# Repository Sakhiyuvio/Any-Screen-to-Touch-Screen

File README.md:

# Any-Screen-to-Touch-Screen

Making any screen of any device to become touch-screen. Utilizing UWB transceivers for location distinction with triangulation and TWR algorithms. Our pen enclosure communicates to host device via Bluetooth HID.

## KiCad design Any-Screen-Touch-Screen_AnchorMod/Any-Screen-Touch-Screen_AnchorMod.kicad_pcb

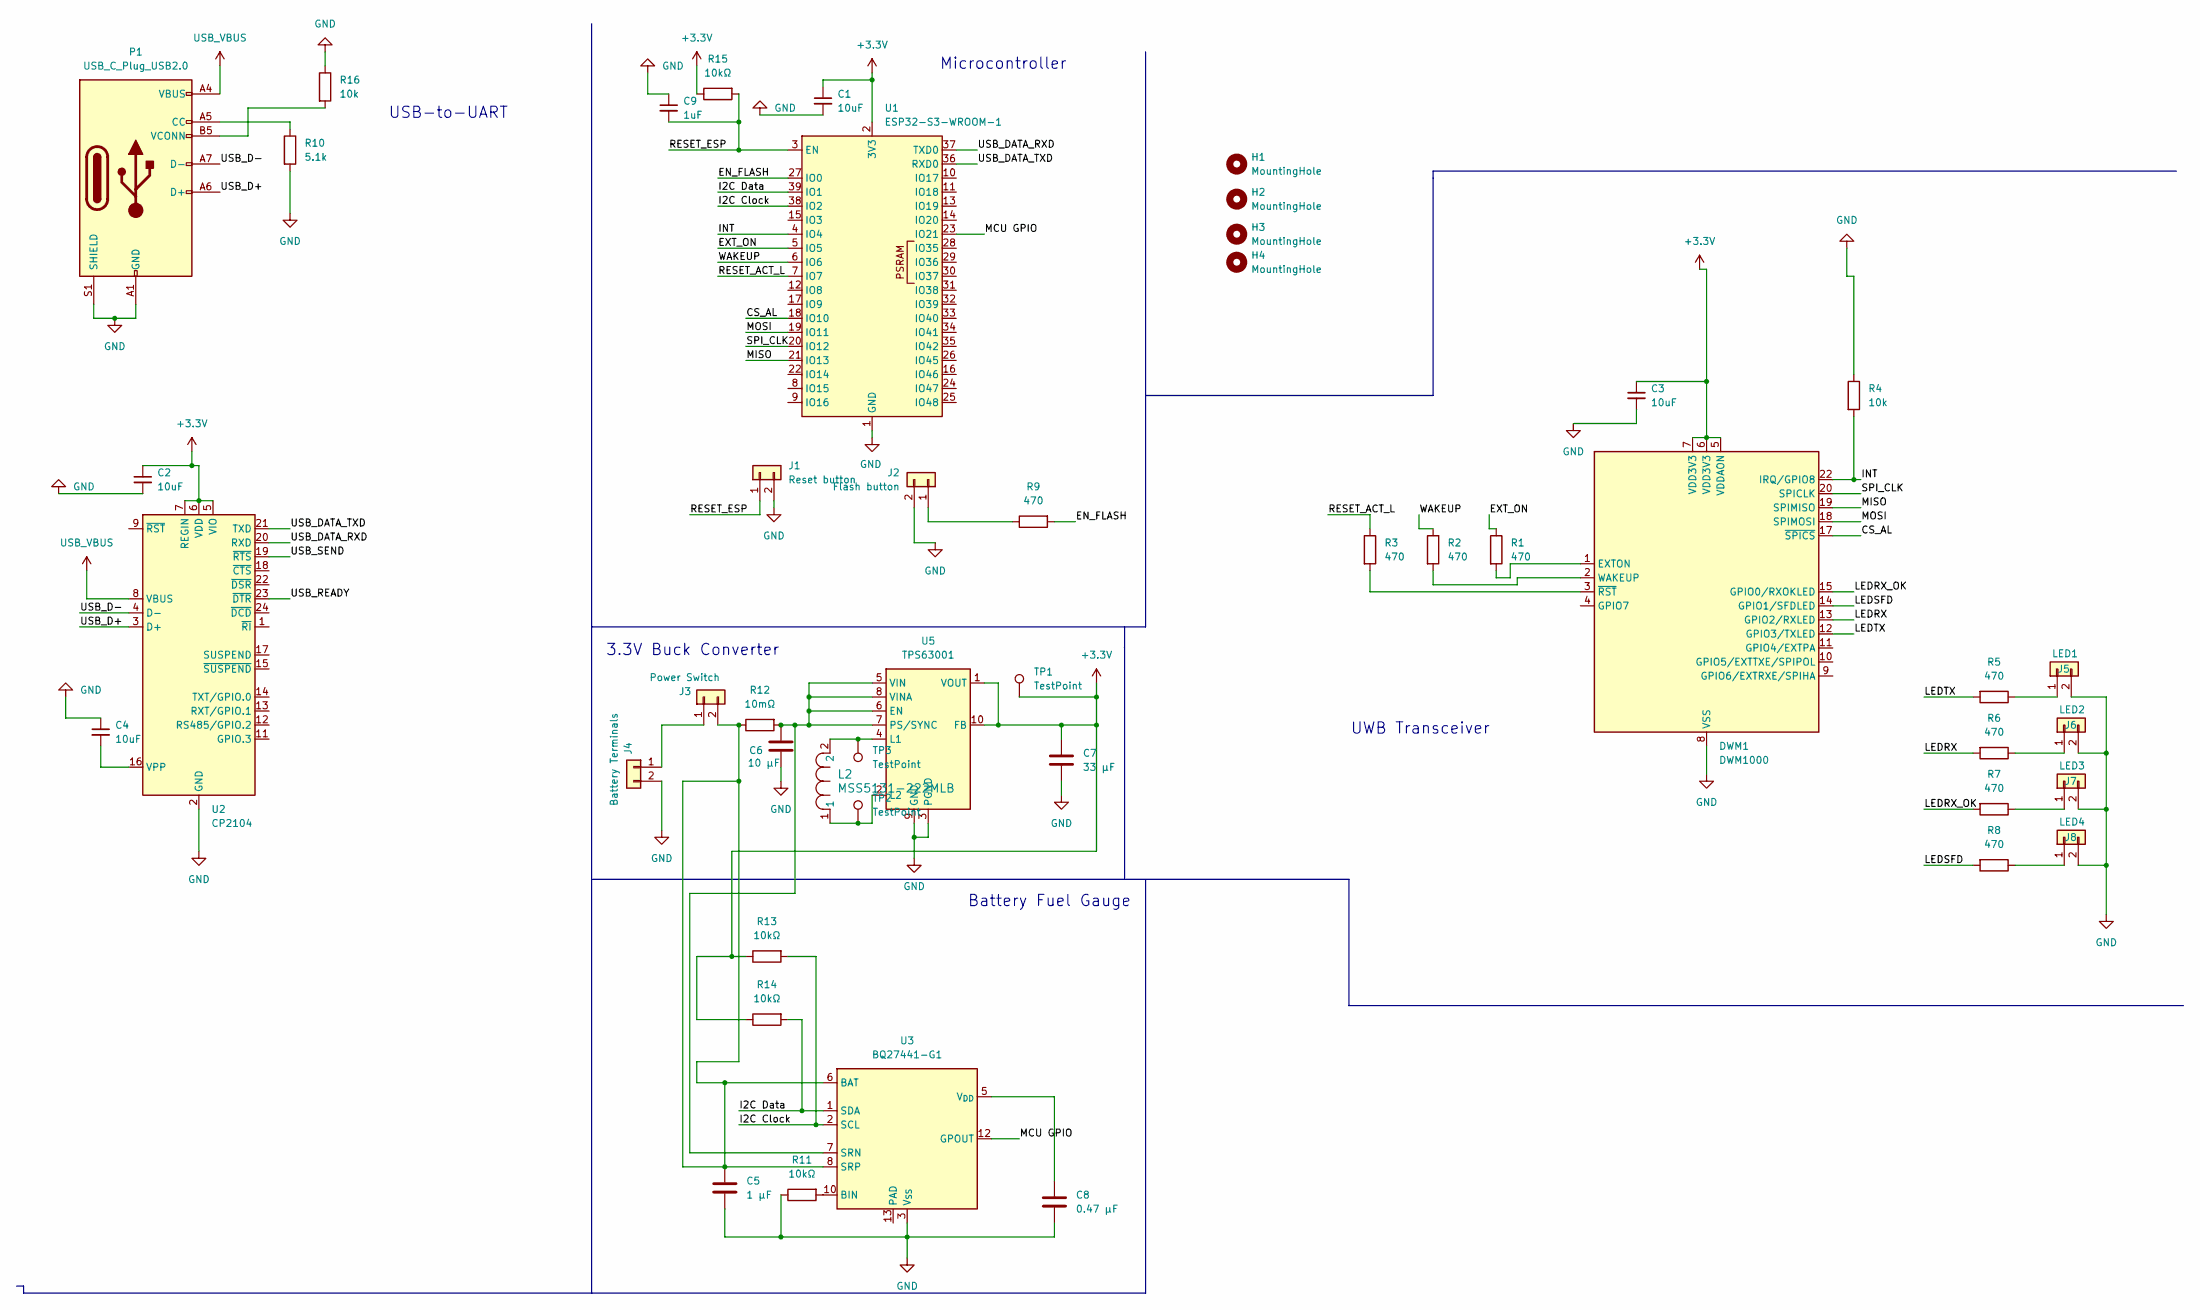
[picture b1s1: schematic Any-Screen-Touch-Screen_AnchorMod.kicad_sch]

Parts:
C1, C2, C3, C4: 10uF; C_0805_2012Metric_Pad1.18x1.45mm_HandSolder
C5: 1 μF; C_0805_2012Metric_Pad1.18x1.45mm_HandSolder
C6: 10 μF; C_0805_2012Metric_Pad1.18x1.45mm_HandSolder
C7: 33 μF; C_0805_2012Metric_Pad1.18x1.45mm_HandSolder
C8: 0.47 μF; C_0805_2012Metric_Pad1.18x1.45mm_HandSolder
C9: 1uF; C_0805_2012Metric_Pad1.18x1.45mm_HandSolder
DWM1: DWM1000
H1, H2, H3, H4: MountingHole; MountingHole_3.2mm_M3
J1: Reset button; Molex_KK-254_AE-6410-02A_1x02_P2.54mm_Vertical
J2: Flash button; Molex_KK-254_AE-6410-02A_1x02_P2.54mm_Vertical
J3: Power Switch; Molex_KK-254_AE-6410-02A_1x02_P2.54mm_Vertical
J4: Battery Terminals; Molex_KK-254_AE-6410-02A_1x02_P2.54mm_Vertical
J5: LED1; Molex_KK-254_AE-6410-02A_1x02_P2.54mm_Vertical
J6: LED2; Molex_KK-254_AE-6410-02A_1x02_P2.54mm_Vertical
J7: LED3; Molex_KK-254_AE-6410-02A_1x02_P2.54mm_Vertical
J8: LED4; Molex_KK-254_AE-6410-02A_1x02_P2.54mm_Vertical
L2: MSS5131-222MLB; IND_MSS5131_COC
P1: USB_C_Plug_USB2.0; USB_C_Plug_Molex_105444
R1, R2, R3, R5, R6, R7, R8, R9: 470; R_0805_2012Metric_Pad1.20x1.40mm_HandSolder
R4, R16: 10k; R_0805_2012Metric_Pad1.20x1.40mm_HandSolder
R10: 5.1k; R_0805_2012Metric_Pad1.20x1.40mm_HandSolder
R11, R13, R14, R15: 10kΩ; R_0805_2012Metric_Pad1.20x1.40mm_HandSolder
R12: 10mΩ; R_0805_2012Metric_Pad1.20x1.40mm_HandSolder
TP1, TP2, TP3: TestPoint; TestPoint_Keystone_5010-5014_Multipurpose
U1: ESP32-S3-WROOM-1
U2: CP2104; QFN-24-1EP_4x4mm_P0.5mm_EP2.7x2.7mm_ThermalVias
U3: BQ27441-G1; Texas_S-PDSO-N12
U5: TPS63001; Texas_DRC0010J_ThermalVias

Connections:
+3.3V: C1.1, C2.1, C3.1, C7.1, DWM1.5 (VDDAON), DWM1.6 (VDD3V3), DWM1.7 (VDD3V3), R13.1, R14.1, R15.1, TP1.1, U1.2 (3V3), U2.5 (VIO), U2.6 (VDD), U2.7 (REGIN), U5.1 (VOUT), U5.10 (FB)
/CS_AL: DWM1.17 (~SPICS), U1.18 (IO10)
/EN_FLASH: R9.2, U1.27 (IO0)
/EXT_ON: R1.1, U1.5 (IO5)
/I2C Clock: R13.2, U1.38 (IO2), U3.2 (SCL)
/I2C Data: R14.2, U1.39 (IO1), U3.1 (SDA)
/INT: DWM1.22 (IRQ/GPIO8), R4.2, U1.4 (IO4)
/LEDRX: DWM1.13 (GPIO2/RXLED), R6.2
/LEDRX_OK: DWM1.15 (GPIO0/RXOKLED), R7.2
/LEDSFD: DWM1.14 (GPIO1/SFDLED), R8.2
/LEDTX: DWM1.12 (GPIO3/TXLED), R5.2
/MCU GPIO: U1.23 (IO21), U3.12 (GPOUT)
/MISO: DWM1.19 (SPIMISO), U1.21 (IO13)
/MOSI: DWM1.18 (SPIMOSI), U1.19 (IO11)
/RESET_ACT_L: R3.1, U1.7 (IO7)
/RESET_ESP: C9.2, J1.1, R15.2, U1.3 (EN)
/SPI_CLK: DWM1.20 (SPICLK), U1.20 (IO12)
/USB_D+: P1.A6 (D+), U2.3 (D+)
/USB_D-: P1.A7 (D-), U2.4 (D-)
/USB_DATA_RXD: U1.37 (TXD0), U2.20 (RXD)
/USB_DATA_TXD: U1.36 (RXD0), U2.21 (TXD)
/USB_READY: U2.23 (~DTR)
/USB_SEND: U2.19 (~RTS)
/WAKEUP: R2.1, U1.6 (IO6)
GND: C1.2, C2.2, C3.2, C4.1, C5.2, C6.1, C7.2, C8.2, C9.1, DWM1.8 (VSS), DWM1.16 (VSS), DWM1.21 (VSS), DWM1.23 (VSS), DWM1.24 (VSS), J1.2, J2.2, J4.2, J5.2, J6.2, J7.2, J8.2, P1.A1 (GND), P1.A12 (GND), P1.B1 (GND), P1.B12 (GND), P1.S1 (SHIELD), R4.1, R10.2, R11.1, R16.1, U1.1 (GND), U1.40 (GND), U1.41 (GND), U2.2 (GND), U2.25 (GND), U3.3 (V_{SS}), U5.3 (PGND), U5.9 (GND), U5.11 (PGND)
unnamed: DWM1.1 (EXTON), R1.2
unnamed: DWM1.2 (WAKEUP), R2.2
unnamed: DWM1.3 (~RST), R3.2
unnamed: J2.1, R9.1
unnamed: J3.1, J4.1
unnamed: C5.1, J3.2, R12.1, U3.6 (BAT), U3.8 (SRP)
unnamed: J5.1, R5.1
unnamed: J6.1, R6.1
unnamed: J7.1, R7.1
unnamed: J8.1, R8.1
unnamed: P1.A5 (CC), R10.1
unnamed: P1.B5 (VCONN), R16.2
unnamed: C4.2, U2.16 (VPP)
unnamed: R11.2, U3.10 (BIN)
unnamed: C6.2, R12.2, U3.7 (SRN), U5.5 (VIN), U5.6 (EN), U5.7 (PS/SYNC), U5.8 (VINA)
unnamed: C8.1, U3.5 (V_{DD})
unnamed: L2.2, TP3.1, U5.4 (L1)
unnamed: L2.1, TP2.1, U5.2 (L2)
USB_VBUS: P1.A4 (VBUS), P1.A9 (VBUS), P1.B4 (VBUS), P1.B9 (VBUS), U2.8 (VBUS)

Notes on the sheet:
USB-to-UART
Microcontroller
3.3V Buck Converter
Battery Fuel Gauge
UWB Transceiver

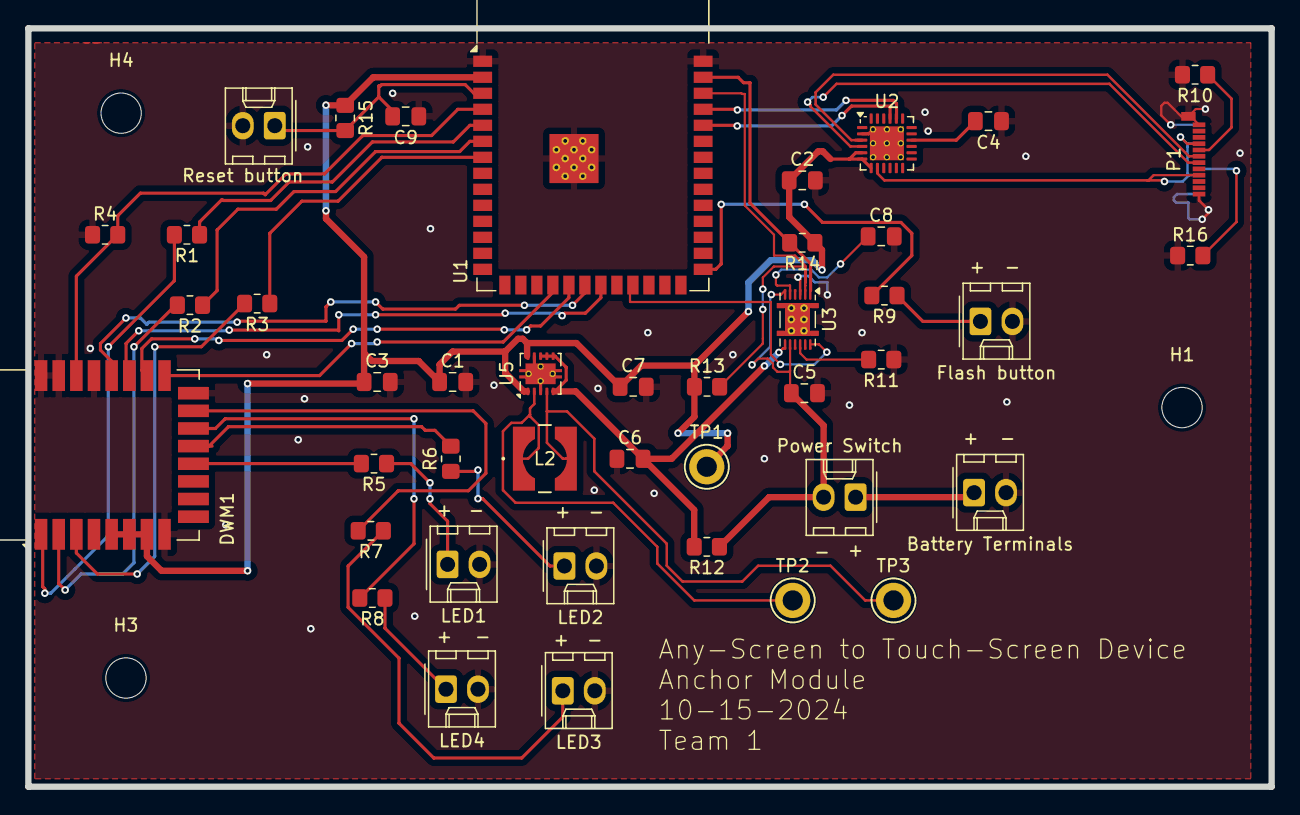
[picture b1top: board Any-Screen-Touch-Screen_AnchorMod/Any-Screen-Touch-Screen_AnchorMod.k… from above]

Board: 2 copper layers, 98.7 x 60.2 mm, 46 parts (0 on the bottom side), 42 nets.

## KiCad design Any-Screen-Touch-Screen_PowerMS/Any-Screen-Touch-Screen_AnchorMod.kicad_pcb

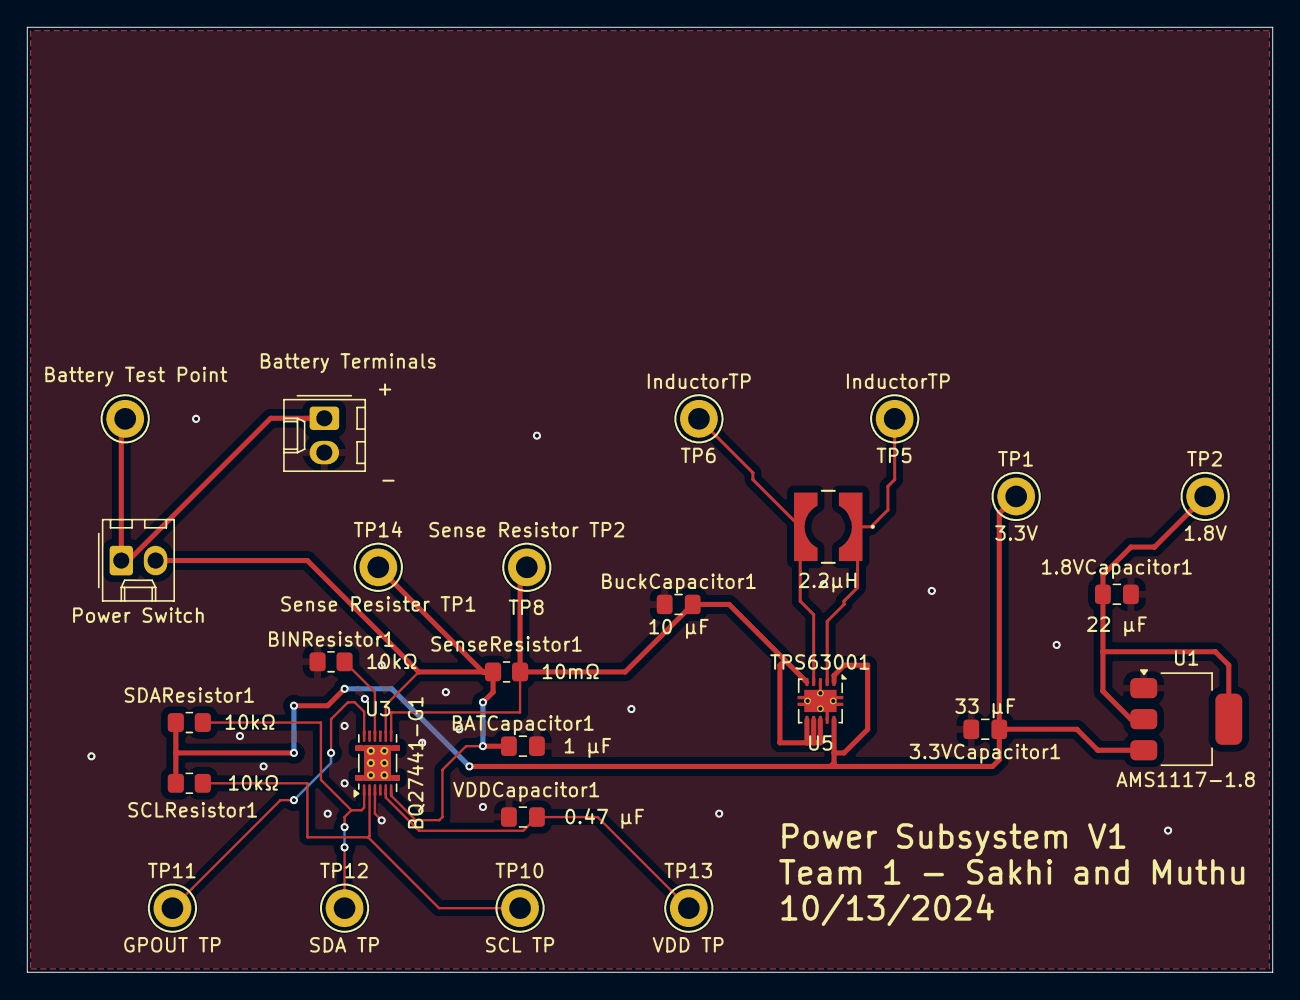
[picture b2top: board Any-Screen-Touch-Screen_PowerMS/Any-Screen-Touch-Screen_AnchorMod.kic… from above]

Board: 2 copper layers, 92.2 x 70.0 mm, 26 parts (0 on the bottom side), 13 nets.

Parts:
1.8VCapacitor1: 22 μF; C_0805_2012Metric_Pad1.18x1.45mm_HandSolder
3.3VCapacitor1: 33 μF; C_0805_2012Metric_Pad1.18x1.45mm_HandSolder
BATCapacitor1: 1 μF; C_0805_2012Metric_Pad1.18x1.45mm_HandSolder
BINResistor1: 10kΩ; R_0805_2012Metric_Pad1.20x1.40mm_HandSolder
BuckCapacitor1: 10 μF; C_0805_2012Metric_Pad1.18x1.45mm_HandSolder
J3: Power Switch; Molex_KK-254_AE-6410-02A_1x02_P2.54mm_Vertical
J4: Battery Terminals; Molex_KK-254_AE-6410-02A_1x02_P2.54mm_Vertical
L1: 2.2μH; IND_MSS5131_COC
SCLResistor1: 10kΩ; R_0805_2012Metric_Pad1.20x1.40mm_HandSolder
SDAResistor1: 10kΩ; R_0805_2012Metric_Pad1.20x1.40mm_HandSolder
SenseResistor1: 10mΩ; R_0805_2012Metric_Pad1.20x1.40mm_HandSolder
TP1: 3.3V; TestPoint_Keystone_5010-5014_Multipurpose
TP2: 1.8V; TestPoint_Keystone_5010-5014_Multipurpose
TP3: Battery Test Point; TestPoint_Keystone_5010-5014_Multipurpose
TP5, TP6: InductorTP; TestPoint_Keystone_5010-5014_Multipurpose
TP8: Sense Resistor TP2; TestPoint_Keystone_5010-5014_Multipurpose
TP10: SCL TP; TestPoint_Keystone_5010-5014_Multipurpose
TP11: GPOUT TP; TestPoint_Keystone_5010-5014_Multipurpose
TP12: SDA TP; TestPoint_Keystone_5010-5014_Multipurpose
TP13: VDD TP; TestPoint_Keystone_5010-5014_Multipurpose
TP14: Sense Resister TP1; TestPoint_Keystone_5010-5014_Multipurpose
U1: AMS1117-1.8; SOT-223-3_TabPin2
U3: BQ27441-G1; Texas_S-PDSO-N12
U5: TPS63001; Texas_DRC0010J_ThermalVias
VDDCapacitor1: 0.47 μF; C_0805_2012Metric_Pad1.18x1.45mm_HandSolder

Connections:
GND: 1.8VCapacitor1.2, 3.3VCapacitor1.2, BATCapacitor1.2, BINResistor1.1, BuckCapacitor1.1, J4.2, U1.1 (GND), U3.3 (V_{SS}), U5.3 (PGND), U5.9 (GND), U5.11 (PGND), VDDCapacitor1.2
unnamed: J3.1, J4.1, TP3.1
unnamed: BATCapacitor1.1, J3.2, SenseResistor1.1, TP14.1, U3.6 (BAT), U3.8 (SRP)
unnamed: 3.3VCapacitor1.1, SCLResistor1.1, SDAResistor1.1, TP1.1, U1.3 (VI), U5.1 (VOUT), U5.10 (FB)
unnamed: 1.8VCapacitor1.1, TP2.1, U1.2 (VO)
unnamed: BINResistor1.2, U3.10 (BIN)
unnamed: TP11.1, U3.12 (GPOUT)
unnamed: SCLResistor1.2, TP10.1, U3.2 (SCL)
unnamed: SDAResistor1.2, TP12.1, U3.1 (SDA)
unnamed: BuckCapacitor1.2, SenseResistor1.2, TP8.1, U3.7 (SRN), U5.5 (VIN), U5.6 (EN), U5.7 (PS/SYNC), U5.8 (VINA)
unnamed: TP13.1, U3.5 (V_{DD}), VDDCapacitor1.1
unnamed: L1.2, TP6.1, U5.4 (L1)
unnamed: L1.1, TP5.1, U5.2 (L2)

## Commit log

2024-10-03 Anchor and Pen Kicad Designs
2024-10-03 pcb designs
2024-10-06 anchor firmware
2024-10-06 anchor firmware - update handler
2024-10-07 pen firmware prog, update on anchor looping
2024-10-10 cleaned up uwb comm
2024-10-21 updated pcb design
2024-10-21 firmware prog
2024-10-21 renamed to pen control
2024-10-30 complementary filter imp
2024-11-03 prog on localization, prob on tilting
2024-11-03 finished localization
2024-11-04 finished bluetooth hid
2024-11-05 finished BLE setup and GUI
2024-11-05 added fw testing, fixed some typos and clean ups
2024-11-05 fixed typos
2024-11-06 fixes
2024-11-06 changes to imu testing
2024-11-07 revert
2024-11-07 verified imu
2024-11-08 prog on localization test, coordinate calc geometry changes
2024-11-09 unit tests written
2024-11-10 designed localization test
2024-11-10 localization and ble mouse works!
2024-11-14 modif
2024-11-14 anchor modif
2024-11-14 pen modif
2024-11-15 fixed compile issues
2024-11-16 added uwb tests
2024-11-19 uwb testing
2024-11-21 antenna calibration + multi-ranging tag anchor comm
2024-11-21 anchor short address modif
2024-11-24 outlier elimination
2024-11-24 anchor auto-calibration done
2024-11-25 integration
2024-11-25 small button testing
2024-11-25 pen button tested
2024-11-27 smoothing filter for uwb
2024-11-30 accuracy maxxing
2024-12-01 fixed ranging logic
2024-12-01 battery gauge firmware
2024-12-02 increasing accuracy
2024-12-03 acceleration thresholding
2024-12-04 working code, integrating battery gauge
2024-12-09 added battery tracking code to anchor firmware
